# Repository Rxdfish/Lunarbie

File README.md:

# Lunarbie

The nighty companion of Starbie! Lunarbie is a tiny keychain sized board that acts like a little pet for your everyday carry.It is the counterpart to Starbie a starter project of the Hackclub Half-Life program

Heavily inspired by this Repo: [have a look](https://github.com/SharKingStudios/Starbie/tree/main)

# What is this

Lunarbie is a project, made for the [Half life](https://halflife.hackclub.com) by Hackclub programm. It is an alternation by earlier mentioned beginner project Starbie. The project itself is a tiny keychain sized board that acts like a pokemon styled pet. 

The Board features a Microcontroller, display, motion sensor, and environmental sensor in a compact PCB design. It is USB powered and easy to build. Its also moon shaped !

# Project status

The project is finished but it is still possible that some additions to this repo will be made, like CAD files or more features for the Lunarbie.

# Detailed description

Lunarbie is able to interact with its holder passively with its environmental and motion sensors or via the buttons on it. It can interact with the holder by changing its built in display. 
(Additionally it is able to detect another Lunarbie (or Starbie) when holding them at each other, similar to apples airdrop feature.)

# Motivation

The main motivation is of course the Half Life (LINK) program by hackclub. It was designed in week one of the project where the task was to create a custom PCB. Other than that, I really wanted to design a PCB for a long time now and it definitely won’t be my last one. It was really fun to design it and challenge me with a fun and beginnerfriendly project that could maybe even be continued.

# Project journaling

Via the [Half life](https://halflife.hackclub.com) by Hackclub programm, several Journal entries have been made either in timelaps form or as written entry to track the project. 

# Assembly

The assembly should be quite beginnerfriendly. The board itself has not many part and is partly prefabricated. All remaining components are easy to be soldered by hand.

# Schematic and components

The board is powered by the XIAO_ESP32C3. It provides the power and data connector with an onboard USB-receptacle. The board also features a MPU6050 motion sensor and an DHT11 environmental sensor. Furthermore it has an Display to broadcast emotions and expressions of the pet. For navigation of the Display and its features, there are two buttons on the board.

# PCB

The PCB is a simple 2 layer PCB with another silkscreen layer for cosmetic purposes. The board also has a GND pour and features routing on the front and backside.

closeup

# Firmware

The firmware is written in the ArduinoIDE and is contained in one singe .ino file. It has some additional features but mainly comes from the starbie repo mentioned above. The firmware can be easily flashed onto the ESP as long as the board has been downloaded in the IDE.

# BOM
The BOM can be viewed in the [BOM.csv](BOM.csv) file 

embedded too: 
Lunarbie – bill of materials
!! The PCB manufacturing was excluded from the list unfortunately because of over budgeting :(
				
| Part | Qty | Unit-Price | total | Shop | Link |
| --- | --- | --- | --- | --- | --- |
| XIAO ESP32 C3 | 1 | $11.33 | $11.33 | AliExpress | [Link](https://www.aliexpress.com/item/1005007084388623.html) |
| 0.96" OLED | 1 | $2.57 | $2.57 | AliExpress | [Link](https://www.aliexpress.com/item/1005009170035050.html) |
| MPU6050 | 1 | $3.61 | $3.61 | AliExpress | [Link](https://www.aliexpress.com/item/32869974009.html) |
| DHT11 | 1 | $1.50 | $1.50 | AliExpress | [Link](https://www.aliexpress.com/item/1005008818897051.html) |
| MX Switches | 1 | $4.27 | $4.27 | AliExpress | [Link](https://www.aliexpress.com/item/1005006161274872.html) |
| Keycaps | 2 | $1.80 | $3.60 | AliExpress | [Link](https://www.aliexpress.com/item/1005007482124353.html) |
| 10k Resistor | 1 | $2.05 | $2.05 | AliExpress | [Link](https://www.aliexpress.com/item/1005004698981340.html) |
| (PCB manufacturing) | 5 | $4 | $4 | JLPCB | [Link](https://cart.jlcpcb.com/de/quote?stencilLayer=2&stencilWidth=100&stencilLength=100&stencilCounts=5&plateType=1&spm=Jlcpcb.Homepage.1010) |
| **Total** | **$28.93** | | Shipping: free | (Shipping for PCB: $8.78) | |

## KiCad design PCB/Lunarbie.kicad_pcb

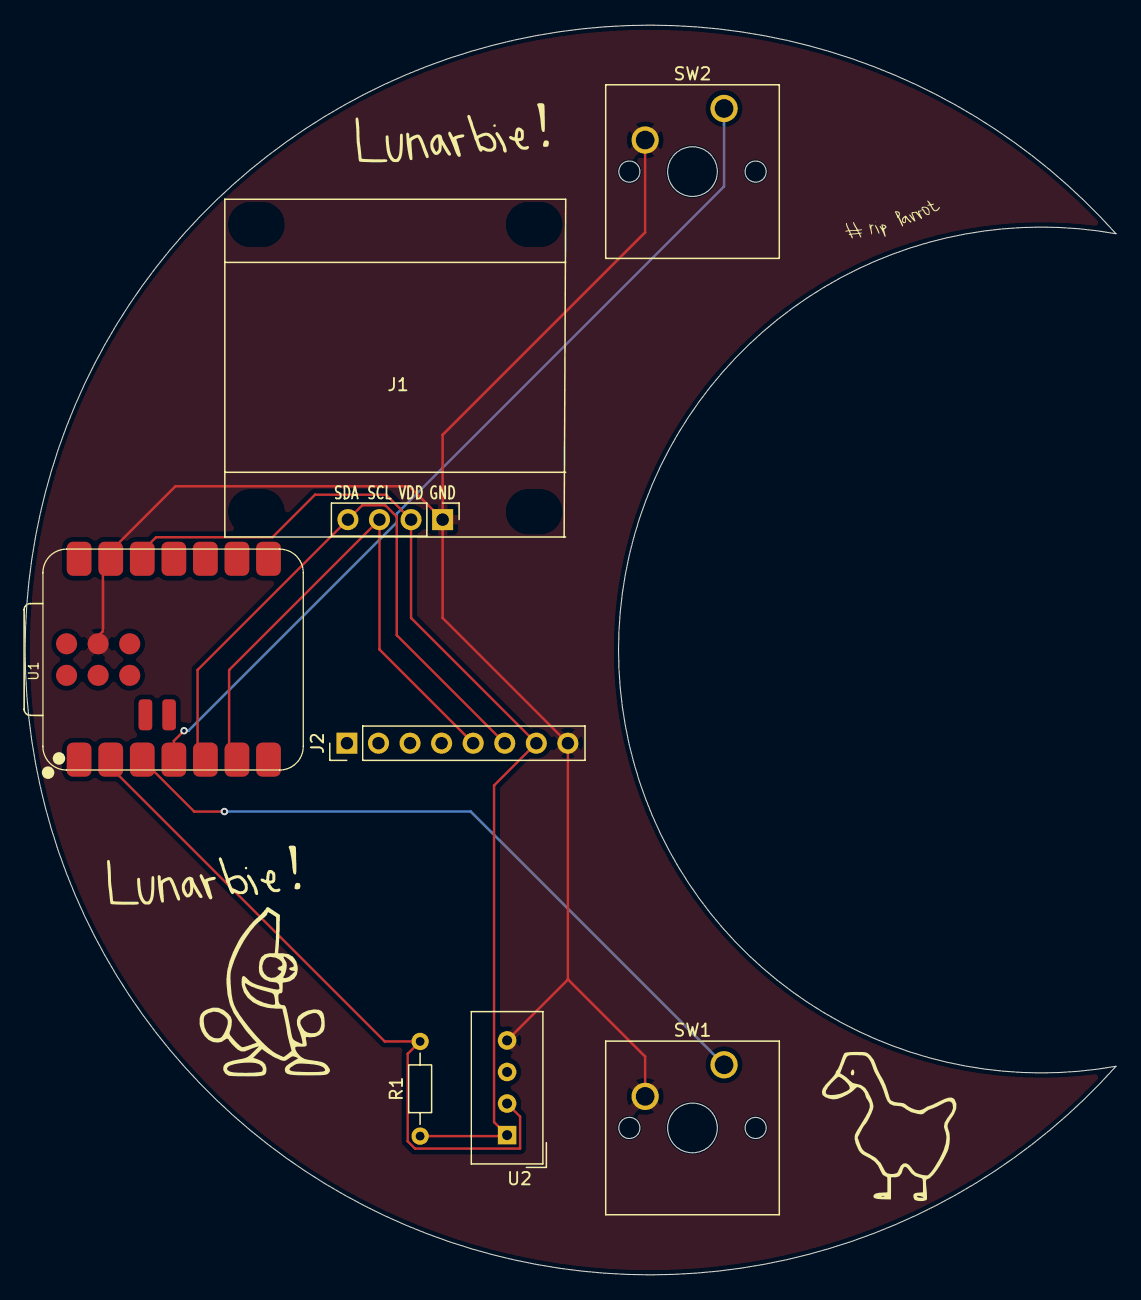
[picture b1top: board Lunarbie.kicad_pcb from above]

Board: 2 copper layers, 87.8 x 100.6 mm, 7 parts (0 on the bottom side), 7 nets.

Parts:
J1: Conn_01x04; Display_128x64_096_I2C
J2: Conn_01x08; PinHeader_1x08_P2.54mm_Vertical
R1: 10k; R_Axial_DIN0204_L3.6mm_D1.6mm_P7.62mm_Horizontal
SW1, SW2: SW_Push; SW_Cherry_MX_1.00u_PCB
U1: XIAO-ESP32-C3-SMD
U2: DHT11; Aosong_DHT11_5.5x12.0_P2.54mm

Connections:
+3.3V: J1.2, J2.7, R1.1, U1.12 (3V3_OUT), U2.1 (VDD)
/DHT11 DATA: R1.2, U1.2 (D1), U2.2 (DATA)
/GPIO2: SW1.1, U1.3 (D2)
/GPIO3: SW2.1, U1.4 (D3)
/SCL: J1.4, J2.6, U1.5 (D4)
/SDA: J1.3, J2.5, U1.6 (D5)
GND: J1.1, J2.8, SW1.2, SW2.2, U1.13 (GND), U1.18 (GND), U2.4 (GND)
